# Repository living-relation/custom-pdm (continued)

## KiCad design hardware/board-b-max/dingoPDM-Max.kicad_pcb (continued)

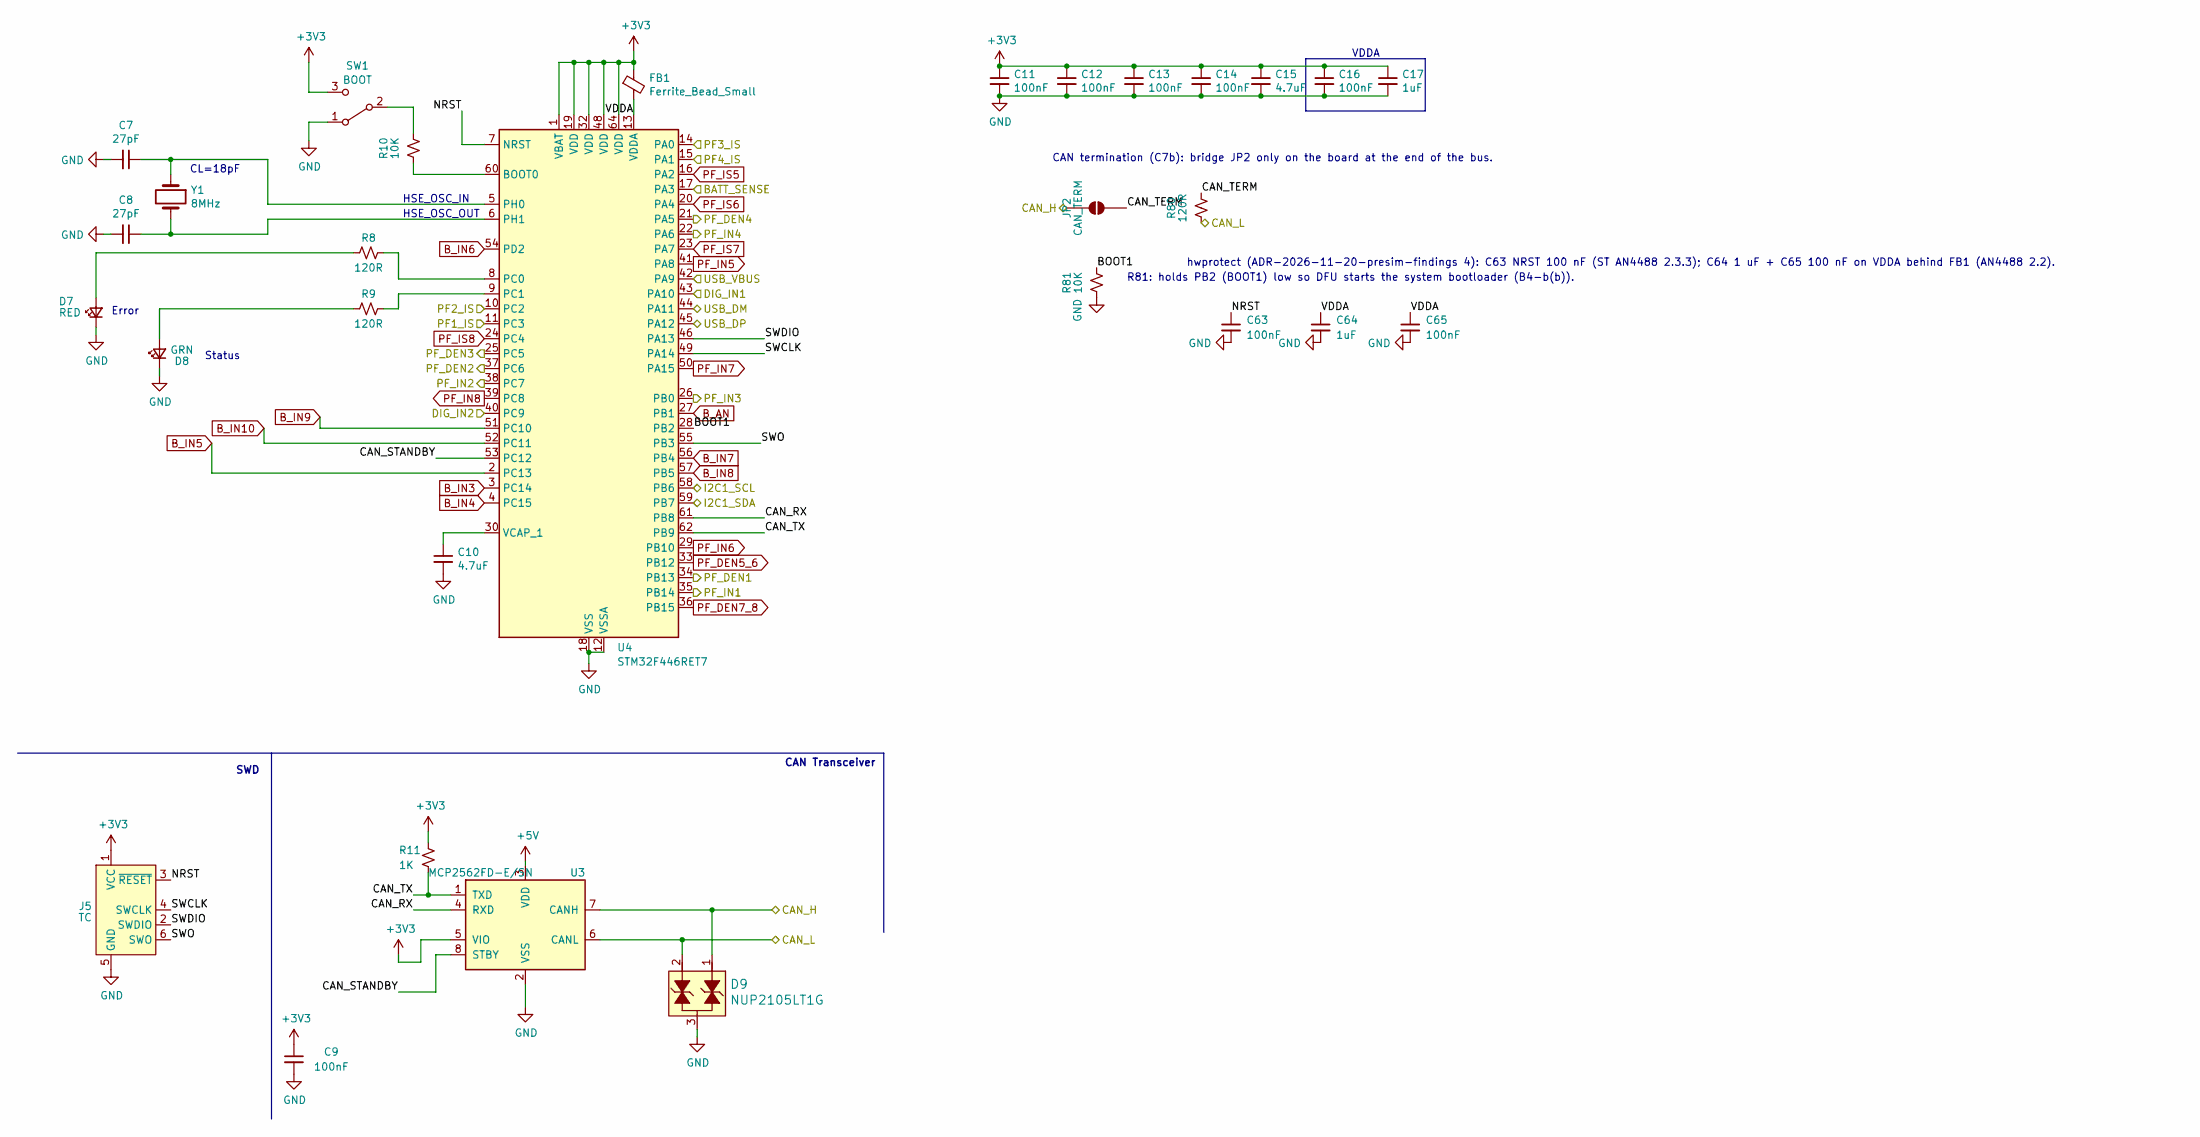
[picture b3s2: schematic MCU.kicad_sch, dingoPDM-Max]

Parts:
C7, C8: 27pF; C_0805_2012Metric; MPN 0805CG270J500NT; Digi-Key_PN 478-10518-1-ND
C9, C11, C12, C13, C14, C16: 100nF; C_0805_2012Metric; MPN CC0805KRX7R9BB104; Digi-Key_PN 478-1395-1-ND
C10, C15: 4.7uF; C_0805_2012Metric; MPN CL21B475KAFNNNE; LCSC C98195
C17: 1uF; C_0805_2012Metric; MPN CL21B105KBFNNNE; Digi-Key_PN 311-1365-1-ND
C63, C65: 100nF; C_0402_1005Metric; MPN CL05B104KO5NNNC; LCSC C1525
C64: 1uF; C_0402_1005Metric; MPN TCC0402X7R105K100AT; LCSC C47325373
D7: RED; LED_0805_2012Metric; MPN LS R976-NR-1-0-20-R18; Digi-Key_PN 475-1278-1-ND
D8: GRN; LED_0805_2012Metric; MPN LG R971-KN-1-0-20-R18; Digi-Key_PN 475-1410-1-ND
D9: NUP2105LT1G; SOT-23-3; MPN NUP2105LT1G; Digi-Key_PN NUP2105LT1GOSCT-ND
FB1: Ferrite_Bead_Small; R_0805_2012Metric; MPN BLM21PG221SN1D; Digi-Key_PN 490-1054-1-ND
J5: TC; Tag-Connect_TC2030-IDC-NL_2x03_P1.27mm_Vertical
JP2: CAN_TERM; SolderJumper-2_P1.3mm_Open_RoundedPad1.0x1.5mm
R8, R9, R80: 120R; R_0805_2012Metric; MPN 0805W8F1200T5E; Digi-Key_PN 311-120CRCT-ND
R10, R81: 10K; R_0805_2012Metric; MPN 0805W8F1002T5E; Digi-Key_PN 311-10.0KCRDKR-ND
R11: 1K; R_0805_2012Metric; MPN 0805W8F1001T5E; Digi-Key_PN 311-1.0KARCT-ND
SW1: BOOT; CJS-1200TB; MPN CJS-1200TB1; Digi-Key_PN 563-CJS-1200TB1CT-ND
U3: MCP2562FD-E/SN; SOIC-8_3.9x4.9mm_P1.27mm; MPN MCP2562FD-E/SN; Digi-Key_PN MCP2562FD-E/SN-ND
U4: STM32F446RET7; LQFP-64_10x10mm_P0.5mm; MPN STM32F446RET7; Digi-Key_PN 497-16775-ND
Y1: 8MHz; Crystal_SMD_5032-2Pin_5.0x3.2mm_HandSoldering; MPN ECS-80-18-30Q-CES-TR; Digi-Key_PN 50-ECS-80-18-30Q-CES-TRCT-ND

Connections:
+3V3: C9.1, C11.1, C12.1, C13.1, C14.1, C15.1, C16.1, C17.1, FB1.1, J5.1 (VCC), R11.2, SW1.3 (C), U3.5 (Vref), U4.1 (VBAT), U4.19 (VDD), U4.32 (VDD), U4.48 (VDD), U4.64 (VDD); also elsewhere on the board
+5V: U3.3 (VDD); also elsewhere on the board
/MCU/BATT_SENSE: U4.17 (PA3); also elsewhere on the board
/MCU/BOOT1: R81.1, U4.28 (PB2)
/MCU/CAN_RX: U3.4 (RXD), U4.61 (PB8)
/MCU/CAN_STANDBY: U3.8 (Rs), U4.53 (PC12)
/MCU/CAN_TERM: JP2.2 (B), R80.1
/MCU/CAN_TX: R11.1, U3.1 (TXD), U4.62 (PB9)
/MCU/NRST: C63.1, J5.3 (~RESET), U4.7 (NRST)
/MCU/SWCLK: J5.4 (SWCLK), U4.49 (PA14)
/MCU/SWDIO: J5.2 (SWDIO), U4.46 (PA13)
/MCU/SWO: J5.6 (SWO), U4.55 (PB3)
/MCU/VDDA: C64.1, C65.1, FB1.2, U4.13 (VDDA)
B_AN: U4.27 (PB1); also elsewhere on the board
B_IN3: U4.3 (PC14); also elsewhere on the board
B_IN4: U4.4 (PC15); also elsewhere on the board
B_IN5: U4.2 (PC13); also elsewhere on the board
B_IN6: U4.54 (PD2); also elsewhere on the board
B_IN7: U4.56 (PB4); also elsewhere on the board
B_IN8: U4.57 (PB5); also elsewhere on the board
B_IN9: U4.51 (PC10); also elsewhere on the board
B_IN10: U4.52 (PC11); also elsewhere on the board
CAN_H: D9.1, JP2.1 (A), U3.7 (CANH); also elsewhere on the board
CAN_L: D9.2, R80.2, U3.6 (CANL); also elsewhere on the board
GND: C7.2, C8.2, C9.2, C10.2, C11.2, C12.2, C13.2, C14.2, C15.2, C16.2, C17.2, C63.2, C64.2, C65.2, D7.1 (K), D8.1 (K), D9.3, J5.5 (GND), R81.2, SW1.1 (A), U3.2 (VSS), U4.12 (VSSA), U4.18 (VSS), U4.31 (VSS), U4.47 (VSS), U4.63 (VSS); also elsewhere on the board
I2C1_SCL: U4.58 (PB6); also elsewhere on the board
I2C1_SDA: U4.59 (PB7); also elsewhere on the board
IN_1: U4.43 (PA10); also elsewhere on the board
IN_2: U4.40 (PC9); also elsewhere on the board
unnamed: D7.2 (A), R8.2
unnamed: D8.2 (A), R9.2
unnamed: R10.1, SW1.2 (B)
unnamed: R10.2, U4.60 (BOOT0)
unnamed: R8.1, U4.8 (PC0)
unnamed: R9.1, U4.9 (PC1)
unnamed: C7.1, U4.5 (PH0), Y1.1
unnamed: C8.1, U4.6 (PH1), Y1.2
unnamed: C10.1, U4.30 (VCAP_1)
PF_DEN1: U4.34 (PB13); also elsewhere on the board
PF_DEN2: U4.37 (PC6); also elsewhere on the board
PF_DEN3: U4.25 (PC5); also elsewhere on the board
PF_DEN4: U4.21 (PA5); also elsewhere on the board
PF_DEN5_6: U4.33 (PB12); also elsewhere on the board
PF_DEN7_8: U4.36 (PB15); also elsewhere on the board
PF_IN1: U4.35 (PB14); also elsewhere on the board
PF_IN2: U4.38 (PC7); also elsewhere on the board
PF_IN3: U4.26 (PB0); also elsewhere on the board
PF_IN4: U4.22 (PA6); also elsewhere on the board
PF_IN5: U4.41 (PA8); also elsewhere on the board
PF_IN6: U4.29 (PB10); also elsewhere on the board
PF_IN7: U4.50 (PA15); also elsewhere on the board
PF_IN8: U4.39 (PC8); also elsewhere on the board
PF_IS1: U4.11 (PC3); also elsewhere on the board
PF_IS2: U4.10 (PC2); also elsewhere on the board
PF_IS3: U4.14 (PA0); also elsewhere on the board
PF_IS4: U4.15 (PA1); also elsewhere on the board
PF_IS5: U4.16 (PA2); also elsewhere on the board
PF_IS6: U4.20 (PA4); also elsewhere on the board
PF_IS7: U4.23 (PA7); also elsewhere on the board
PF_IS8: U4.24 (PC4); also elsewhere on the board
USB_D+: U4.45 (PA12); also elsewhere on the board
USB_D-: U4.44 (PA11); also elsewhere on the board
USB_VBUS: U4.42 (PA9); also elsewhere on the board

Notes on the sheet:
SWD
Error
CAN Transceiver
HSE_OSC_IN
CL=18pF
HSE_OSC_OUT
VDDA
Status
CAN termination (C7b): bridge JP2 only on the board at the end of the bus.
R81: holds PB2 (BOOT1) low so DFU starts the system bootloader (B4-b(b)).
hwprotect (ADR-2026-11-20-presim-findings 4): C63 NRST 100 nF (ST AN4488 2.3.3); C64 1 uF + C65 100 nF on VDDA behind FB1 (AN4488 2.2).

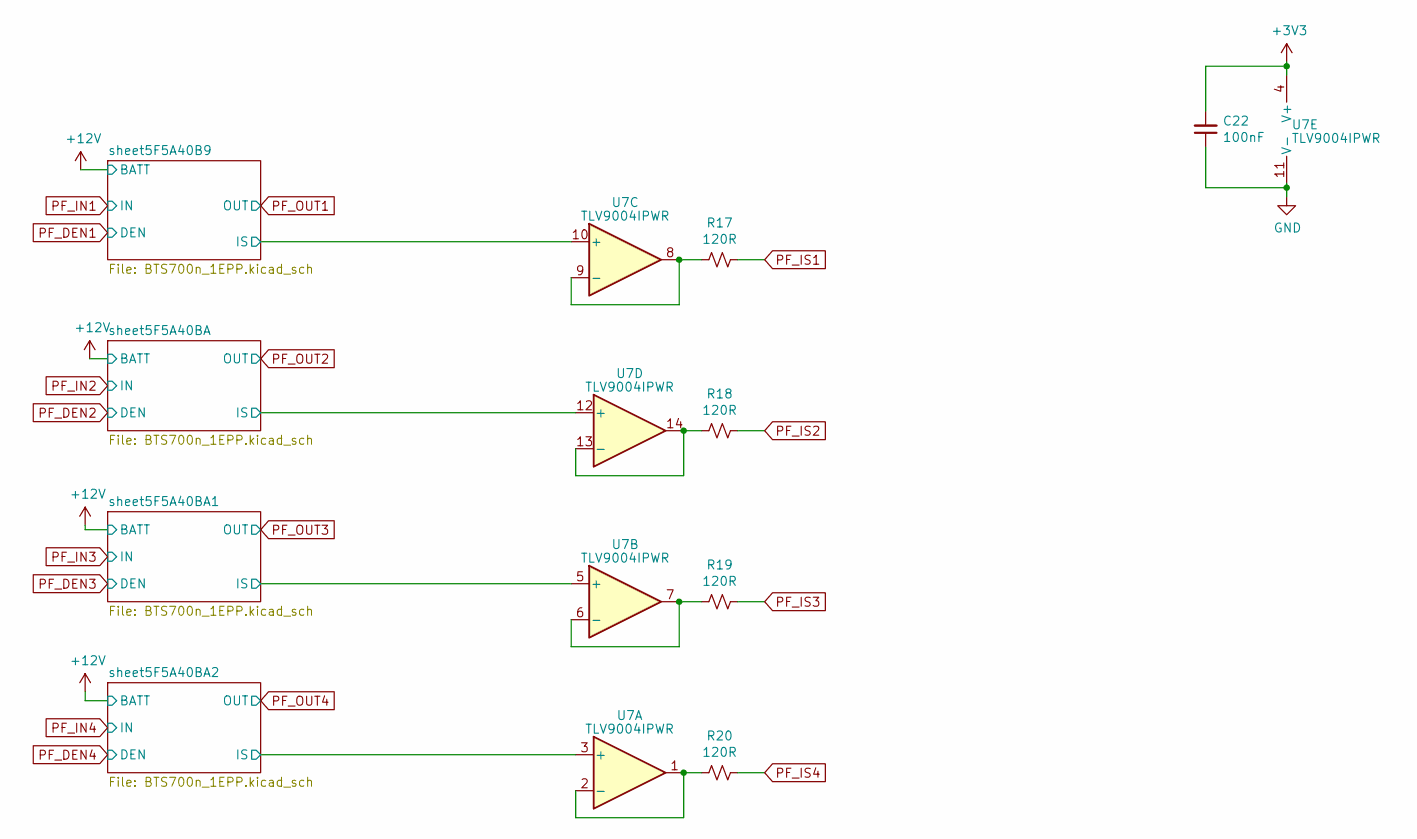
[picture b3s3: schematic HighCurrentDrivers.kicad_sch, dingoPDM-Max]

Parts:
C22: 100nF; C_0805_2012Metric; MPN CC0805KRX7R9BB104; Digi-Key_PN 478-1395-1-ND
R17, R18, R19, R20: 120R; R_0805_2012Metric; MPN 0805W8F1200T5E; Digi-Key_PN 311-120CRCT-ND
U7: TLV9004IPWR; TSSOP-14_4.4x5mm_P0.65mm; MPN TLV9004IPWR; Digi-Key_PN 296-51827-1-ND

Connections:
+3V3: C22.2, U7.4 (V+); also elsewhere on the board
/HighCurrentDrivers/sheet5F5A40B9/IS: U7.10 (+); also elsewhere on the board
/HighCurrentDrivers/sheet5F5A40BA1/IS: U7.5 (+); also elsewhere on the board
/HighCurrentDrivers/sheet5F5A40BA2/IS: U7.3 (+); also elsewhere on the board
/HighCurrentDrivers/sheet5F5A40BA/IS: U7.12 (+); also elsewhere on the board
GND: C22.1, U7.11 (V-); also elsewhere on the board
unnamed: R20.2, U7.1, U7.2 (-)
unnamed: R19.2, U7.6 (-), U7.7
unnamed: R17.2, U7.8, U7.9 (-)
unnamed: R18.2, U7.13 (-), U7.14
PF_IS1: R17.1; also elsewhere on the board
PF_IS2: R18.1; also elsewhere on the board
PF_IS3: R19.1; also elsewhere on the board
PF_IS4: R20.1; also elsewhere on the board

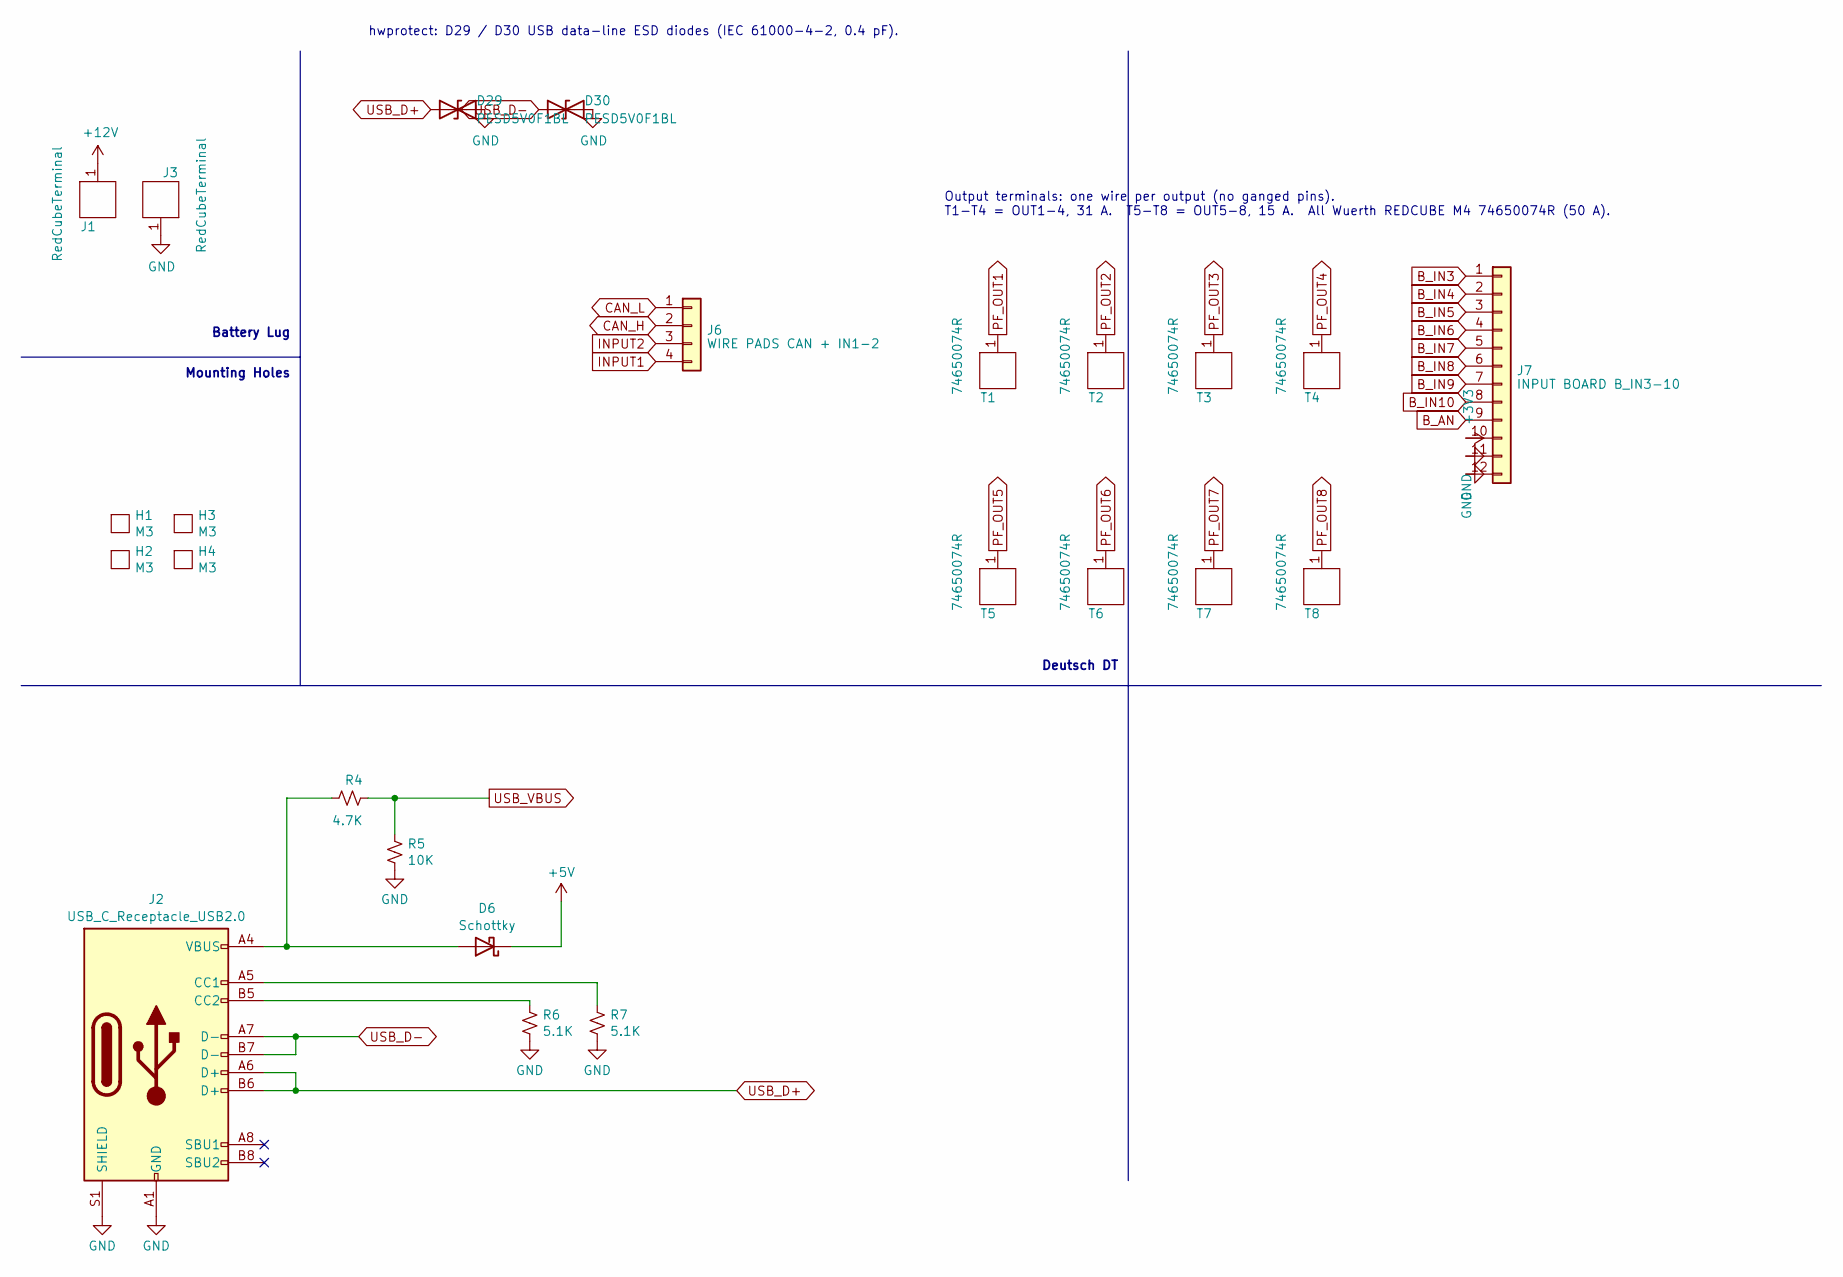
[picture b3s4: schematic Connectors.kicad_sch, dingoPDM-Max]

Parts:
D6: Schottky; D_SOD-123; MPN PMEG10010ELRX; Digi-Key_PN 1727-2394-1-ND
D29, D30: PESD5V0F1BL; D_SOD-882; MPN PESD5V0F1BL,315; LCSC C45961
H1, H2, H3, H4: M3; MountingHole_3.2mm_M3_ISO7380_Pad
J1, J3: RedCubeTerminal; M6_Hole_8Pin_7461084; MPN 7461084; Digi-Key_PN 732-3203-ND
J2: USB_C_Receptacle_USB2.0; USB_C_Receptacle_GCT_USB4085; MPN USB4085-GF-A; Digi-Key_PN 2073-USB4085-GF-ACT-ND
J6: WIRE PADS CAN + IN1-2; MicroFit_2x02_WirePads
J7: INPUT BOARD B_IN3-10; JST_GH_BM12B-GHS-TBT_1x12-1MP_P1.25mm_Vertical; MPN BM12B-GHS-TBT; LCSC C20089173
R4: 4.7K; R_0805_2012Metric; MPN 0805W8F4701T5E; Digi-Key_PN 311-4.70KCRCT-ND
R5: 10K; R_0805_2012Metric; MPN 0805W8F1002T5E; Digi-Key_PN 311-10.0KCRDKR-ND
R6, R7: 5.1K; R_0805_2012Metric; MPN ARG05FTC5101; Digi-Key_PN 311-5.1KARCT-ND
T1, T2, T3, T4, T5, T6, T7, T8: 74650074R; Wuerth_REDCUBE-THR_WP-THRBU_74650074_THR; MPN 74650074R; Digi-Key_PN 732-74650074RCT-ND

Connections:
+3V3: J7.10; also elsewhere on the board
+5V: D6.1 (K); also elsewhere on the board
+12V: J1.1; also elsewhere on the board
B_AN: J7.9; also elsewhere on the board
B_IN3: J7.1; also elsewhere on the board
B_IN4: J7.2; also elsewhere on the board
B_IN5: J7.3; also elsewhere on the board
B_IN6: J7.4; also elsewhere on the board
B_IN7: J7.5; also elsewhere on the board
B_IN8: J7.6; also elsewhere on the board
B_IN9: J7.7; also elsewhere on the board
B_IN10: J7.8; also elsewhere on the board
CAN_H: J6.2; also elsewhere on the board
CAN_L: J6.1; also elsewhere on the board
GND: D29.2 (A2), D30.2 (A2), J2.A1 (GND), J2.A12 (GND), J2.B1 (GND), J2.B12 (GND), J2.S1 (SHIELD), J3.1, J7.11, J7.12, R5.2, R6.2, R7.2; also elsewhere on the board
INPUT1: J6.4; also elsewhere on the board
INPUT2: J6.3; also elsewhere on the board
unnamed: D6.2 (A), J2.A4 (VBUS), J2.A9 (VBUS), J2.B4 (VBUS), J2.B9 (VBUS), R4.1
unnamed: J2.A5 (CC1), R7.1
unnamed: J2.B5 (CC2), R6.1
PF_OUT1: T1.1; also elsewhere on the board
PF_OUT2: T2.1; also elsewhere on the board
PF_OUT3: T3.1; also elsewhere on the board
PF_OUT4: T4.1; also elsewhere on the board
PF_OUT5: T5.1; also elsewhere on the board
PF_OUT6: T6.1; also elsewhere on the board
PF_OUT7: T7.1; also elsewhere on the board
PF_OUT8: T8.1; also elsewhere on the board
USB_D+: D29.1 (A1), J2.A6 (D+), J2.B6 (D+); also elsewhere on the board
USB_D-: D30.1 (A1), J2.A7 (D-), J2.B7 (D-); also elsewhere on the board
USB_VBUS: R4.2, R5.1; also elsewhere on the board

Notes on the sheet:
Deutsch DT
Battery Lug
Mounting Holes
Output terminals: one wire per output (no ganged pins). T1-T4 = OUT1-4, 31 A. T5-T8 = OUT5-8, 15 A. All Wuerth REDCUBE M4 74650074R (50 A).
hwprotect: D29 / D30 USB data-line ESD diodes (IEC 61000-4-2, 0.4 pF).

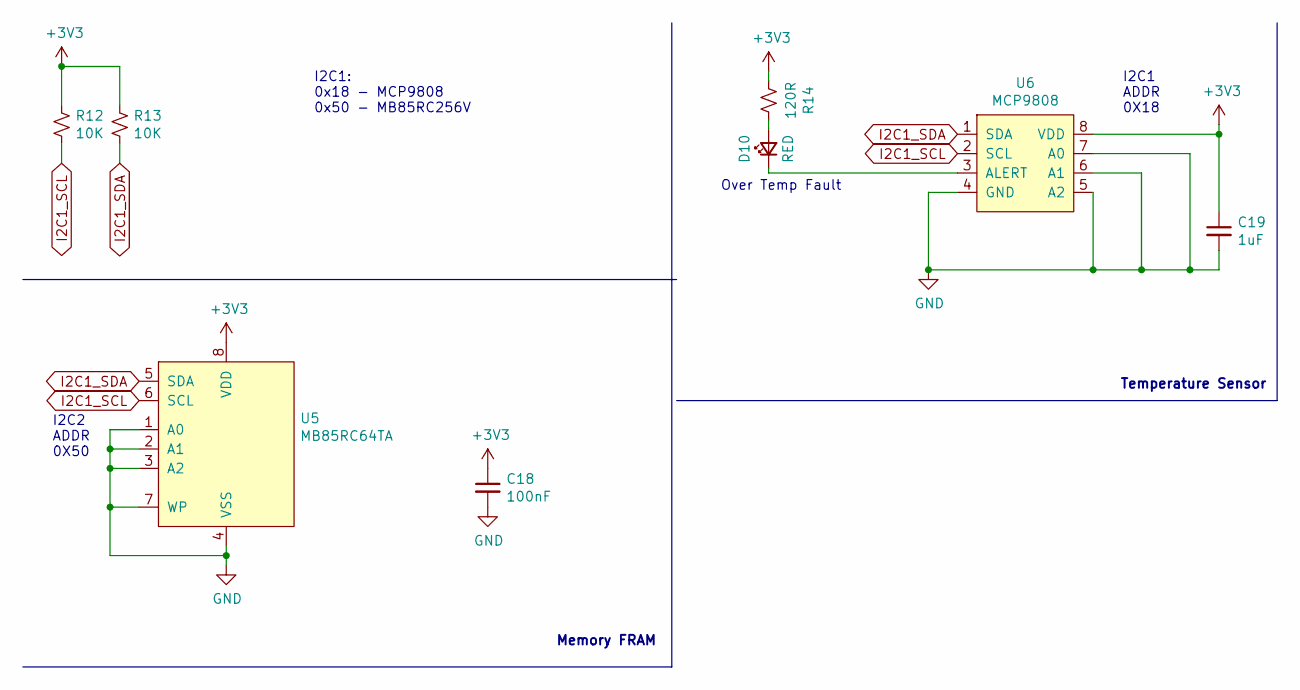
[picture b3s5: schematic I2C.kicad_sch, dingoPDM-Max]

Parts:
C18: 100nF; C_0805_2012Metric; MPN CC0805KRX7R9BB104; Digi-Key_PN 478-1395-1-ND
C19: 1uF; C_0805_2012Metric; MPN CL21B105KBFNNNE; Digi-Key_PN 311-1365-1-ND
D10: RED; LED_0805_2012Metric; MPN LS R976-NR-1-0-20-R18; Digi-Key_PN 475-1278-1-ND
R12, R13: 10K; R_0805_2012Metric; MPN 0805W8F1002T5E; Digi-Key_PN 311-10.0KCRDKR-ND
R14: 120R; R_0805_2012Metric; MPN 0805W8F1200T5E; Digi-Key_PN 311-120CRCT-ND
U5: MB85RC64TA; SOIC-8_3.9x4.9mm_P1.27mm; MPN MB85RC64TAPNF-G-AWERE2; Digi-Key_PN 865-MB85RC64TAPNF-G-AWERE2TR-ND
U6: MCP9808; MSOP-8_3x3mm_P0.65mm; MPN MCP9808T-E/MS; Digi-Key_PN MCP9808T-E/MSCT-ND

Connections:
+3V3: C18.1, C19.1, R12.1, R13.1, R14.2, U5.8 (VDD), U6.8 (VDD); also elsewhere on the board
GND: C18.2, C19.2, U5.1 (A0), U5.2 (A1), U5.3 (A2), U5.4 (VSS), U5.7 (WP), U6.4 (GND), U6.5 (A2), U6.6 (A1), U6.7 (A0); also elsewhere on the board
I2C1_SCL: R12.2, U5.6 (SCL), U6.2 (SCL); also elsewhere on the board
I2C1_SDA: R13.2, U5.5 (SDA), U6.1 (SDA); also elsewhere on the board
unnamed: D10.2 (A), R14.1
unnamed: D10.1 (K), U6.3 (ALERT)

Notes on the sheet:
I2C1 ADDR 0X18
I2C2 ADDR 0X50
Over Temp Fault
Temperature Sensor
I2C1: 0x18 - MCP9808 0x50 - MB85RC256V
Memory FRAM

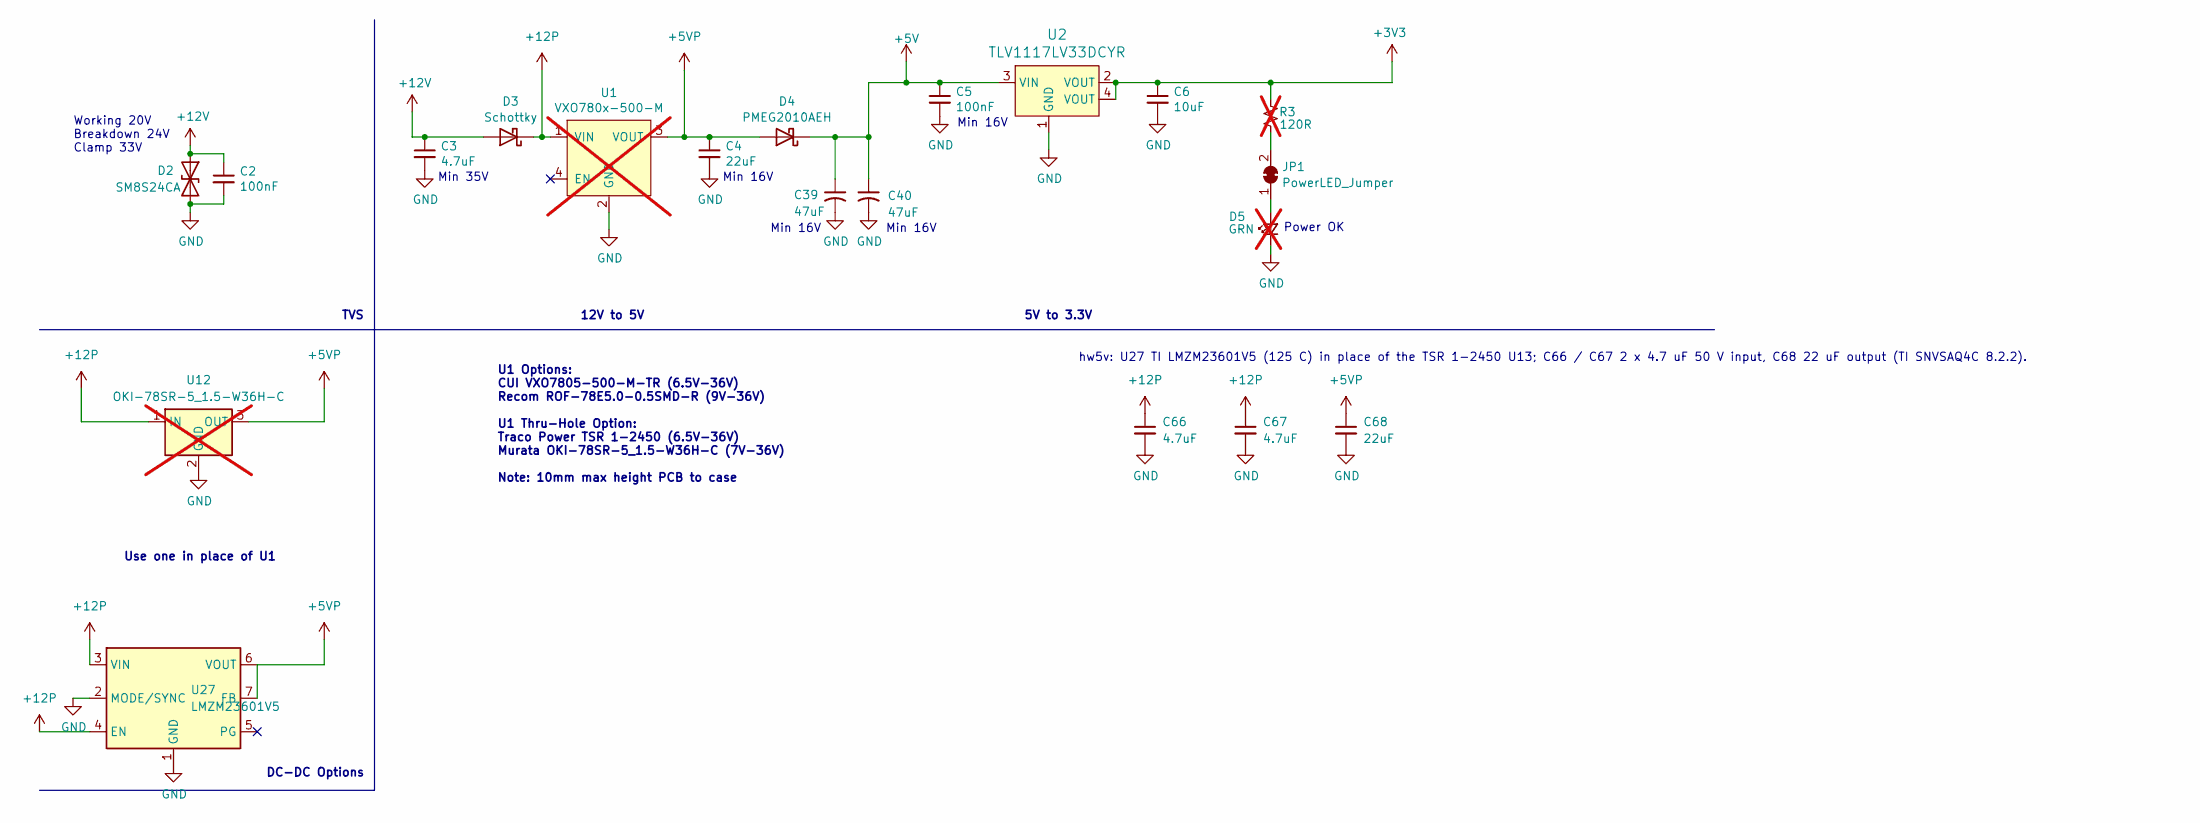
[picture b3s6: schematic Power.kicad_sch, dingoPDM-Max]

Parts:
C2, C5: 100nF; C_0805_2012Metric; MPN CC0805KRX7R9BB104; Digi-Key_PN 478-1395-1-ND
C3, C66, C67: 4.7uF; C_0805_2012Metric; MPN CGA4J1X7R1H475KT0Y0N; LCSC C694229
C4, C68: 22uF; C_0805_2012Metric; MPN GRM21BZ71A226ME15L; LCSC C907991
C6: 10uF; C_0805_2012Metric; MPN CL21B106KPQNNNE; LCSC C32635
C39, C40: 47uF; C_2220_5750Metric; MPN FS55X476K250LRG; Digi-Key_PN 445-7935-1-ND
D2: SM8S24CA; D_DO-218AB_Vishay_SM8S; MPN SM8S24CA-Q; Digi-Key_PN SM8S24CA-QCT-ND
D3: Schottky; D_SOD-123; MPN PMEG10010ELRX; Digi-Key_PN 1727-2394-1-ND
D4: PMEG2010AEH; D_SOD-123F; MPN PMEG2010AEH,115; Digi-Key_PN 1727-PMEG2010AEH,115CT-ND
D5: GRN; LED_0805_2012Metric; MPN LG R971-KN-1-0-20-R18; Digi-Key_PN 475-1410-1-ND; not fitted
JP1: PowerLED_Jumper; SolderJumper-2_P1.3mm_Bridged_RoundedPad1.0x1.5mm
R3: 120R; R_0805_2012Metric; MPN 0805W8F1200T5E; Digi-Key_PN 311-120CRCT-ND; not fitted
U1: VXO780x-500-M; VXO78x-500-M; MPN VXO7805-500-M-TR; Digi-Key_PN 102-VXO7805-500-M-CT-ND; not fitted
U2: TLV1117LV33DCYR; SOT-223; MPN TLV1117LV33DCYR; Digi-Key_PN 296-28778-1-ND
U12: OKI-78SR-5_1.5-W36H-C; Converter_DCDC_Murata_OKI-78SR_Horizontal; MPN OKI-78SR-5/1.5-W36H-C; Digi-Key_PN 811-2692-ND; not fitted
U27: LMZM23601V5; Texas_SIL0010A_MicroSiP-10-1EP_3.8x3mm_P0.6mm_EP0.7x2.9mm_TI; MPN LMZM23601V5SILR; LCSC C2868357

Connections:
+3V3: C6.1, R3.2, U2.2 (VOUT), U2.4 (VOUT); also elsewhere on the board
+5V: C5.1, C39.1, C40.1, D4.1 (K), U2.3 (VIN); also elsewhere on the board
+5VP: C4.1, C68.1, D4.2 (A), U1.3 (VOUT), U12.3 (OUT), U27.6 (VOUT), U27.7 (FB)
+12P: C66.1, C67.1, D3.1 (K), U1.1 (VIN), U12.1 (IN), U27.3 (VIN), U27.4 (EN)
+12V: C2.1, C3.1, D2.1 (A1), D3.2 (A); also elsewhere on the board
GND: C2.2, C3.2, C4.2, C5.2, C6.2, C39.2, C40.2, C66.2, C67.2, C68.2, D2.2 (A2), D5.1 (K), U1.2 (GND), U2.1 (GND), U12.2 (GND), U27.1 (GND), U27.2 (MODE/SYNC), U27.11 (GND); also elsewhere on the board
unnamed: D5.2 (A), JP1.1 (A)
unnamed: JP1.2 (B), R3.1

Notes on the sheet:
Min 16V
TVS
Min 35V
Power OK
Use one in place of U1
5V to 3.3V
12V to 5V
Working 20V Breakdown 24V Clamp 33V
DC-DC Options
U1 Options: CUI VXO7805-500-M-TR (6.5V-36V) Recom ROF-78E5.0-0.5SMD-R (9V-36V) U1 Thru-Hole Option: Traco Power TSR 1-2450 (6.5V-36V) Murata OKI-78SR-5_1.5-W36H-C (7V-36V) Note: 10mm max height PCB to case
hw5v: U27 TI LMZM23601V5 (125 C) in place of the TSR 1-2450 U13; C66 / C67 2 x 4.7 uF 50 V input, C68 22 uF output (TI SNVSAQ4C 8.2.2).

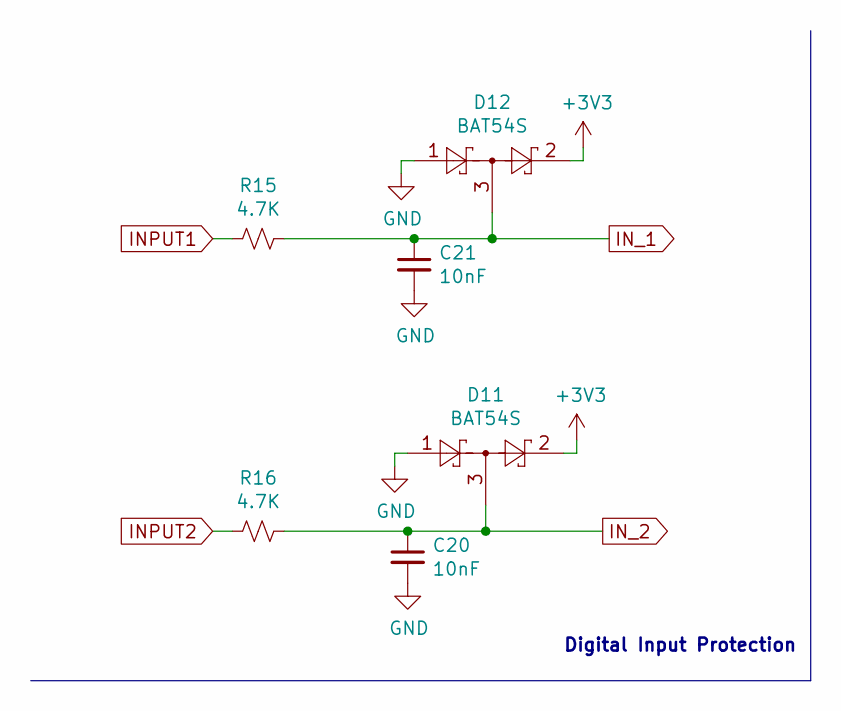
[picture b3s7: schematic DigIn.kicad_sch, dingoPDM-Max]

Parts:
C20, C21: 10nF; C_0805_2012Metric; MPN CL21B103KBANNNC; Digi-Key_PN 311-1136-1-ND
D11, D12: BAT54S; SOT-23; MPN BAT54S,215; Digi-Key_PN BAT54SLT1GOSCT-ND
R15, R16: 4.7K; R_0805_2012Metric; MPN 0805W8F4701T5E; Digi-Key_PN 311-4.70KCRCT-ND

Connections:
+3V3: D11.2, D12.2; also elsewhere on the board
GND: C20.2, C21.2, D11.1, D12.1; also elsewhere on the board
INPUT1: R15.2; also elsewhere on the board
INPUT2: R16.2; also elsewhere on the board
IN_1: C21.1, D12.3, R15.1; also elsewhere on the board
IN_2: C20.1, D11.3, R16.1; also elsewhere on the board

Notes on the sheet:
Digital Input Protection

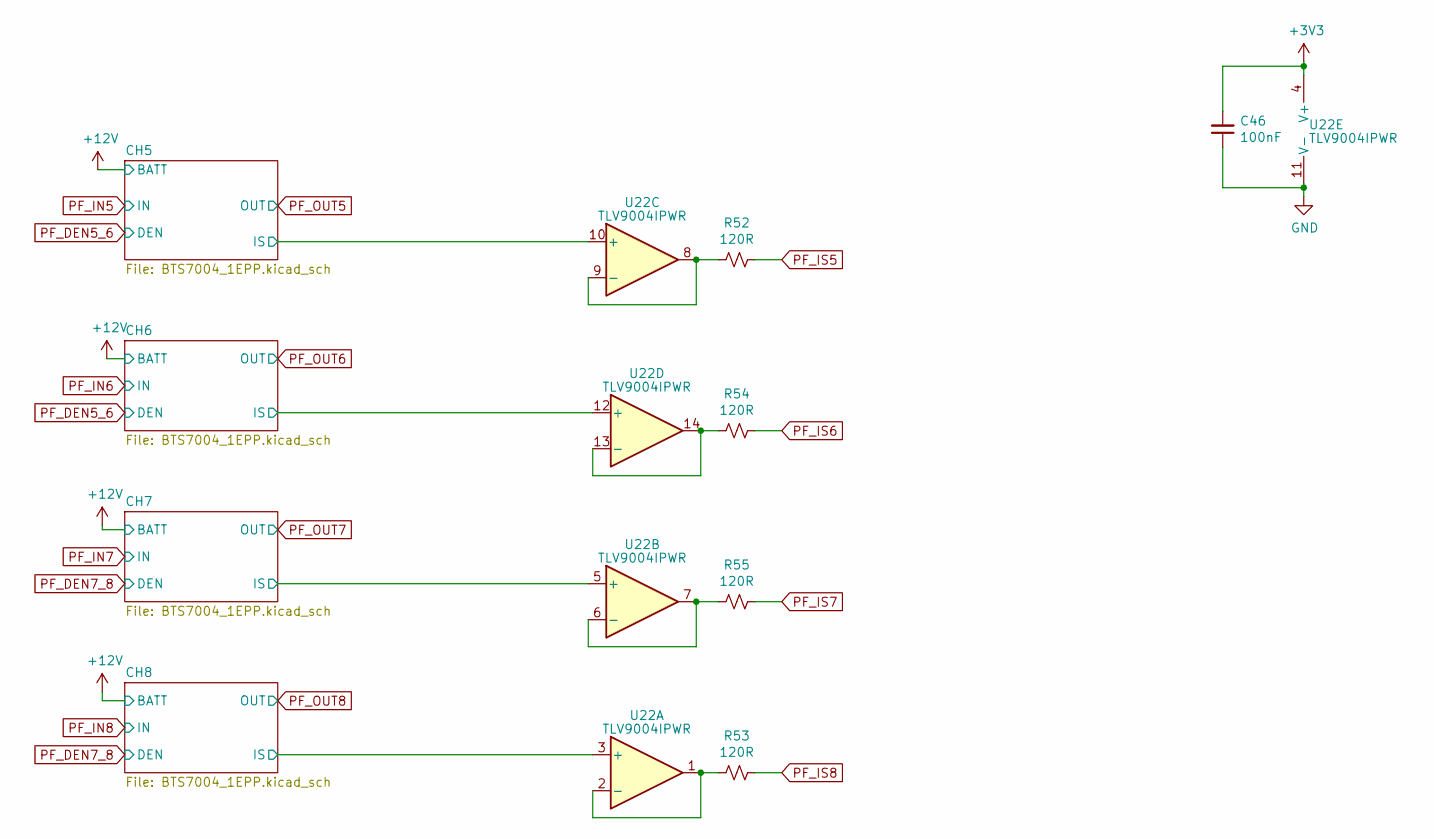
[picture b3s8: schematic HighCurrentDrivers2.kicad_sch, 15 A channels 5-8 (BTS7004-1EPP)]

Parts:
C46: 100nF; C_0805_2012Metric; MPN CC0805KRX7R9BB104; Digi-Key_PN 478-1395-1-ND
R52, R53, R54, R55: 120R; R_0805_2012Metric; MPN 0805W8F1200T5E; Digi-Key_PN 311-120CRCT-ND
U22: TLV9004IPWR; TSSOP-14_4.4x5mm_P0.65mm; MPN TLV9004IPWR; Digi-Key_PN 296-51827-1-ND

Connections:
+3V3: C46.2, U22.4 (V+); also elsewhere on the board
/HighCurrentDrivers2/CH5/IS: U22.10 (+); also elsewhere on the board
/HighCurrentDrivers2/CH6/IS: U22.12 (+); also elsewhere on the board
/HighCurrentDrivers2/CH7/IS: U22.5 (+); also elsewhere on the board
/HighCurrentDrivers2/CH8/IS: U22.3 (+); also elsewhere on the board
GND: C46.1, U22.11 (V-); also elsewhere on the board
unnamed: R53.2, U22.1, U22.2 (-)
unnamed: R55.2, U22.6 (-), U22.7
unnamed: R52.2, U22.8, U22.9 (-)
unnamed: R54.2, U22.13 (-), U22.14
PF_IS5: R52.1; also elsewhere on the board
PF_IS6: R54.1; also elsewhere on the board
PF_IS7: R55.1; also elsewhere on the board
PF_IS8: R53.1; also elsewhere on the board

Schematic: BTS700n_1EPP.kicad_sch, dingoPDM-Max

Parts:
C23: 47nF; C_0805_2012Metric; MPN C0805C473K5RAC7800; Digi-Key_PN 399-C0805C473K5RACTUCT-ND
C24: 100nF; C_0805_2012Metric; MPN CC0805KRX7R9BB104; Digi-Key_PN 478-1395-1-ND
C25: 10nF; C_0805_2012Metric; MPN CL21B103KBANNNC; Digi-Key_PN 311-1136-1-ND
C26: 220pF; C_0805_2012Metric; MPN CC0805GRNPO0BN221; Digi-Key_PN 399-1138-1-ND
D13: BYG23M; DO-214AC; MPN BYG23M-E3/TR; Digi-Key_PN BYG23M-E3/TR3GICT-ND
D14: 5.1V; D_SOD-323_HandSoldering; MPN PDZ5.1B,115; Digi-Key_PN 1727-5155-1-ND
R21, R22, R25, R26: 4.7K; R_0805_2012Metric; MPN 0805W8F4701T5E; Digi-Key_PN 311-4.70KCRCT-ND
R23: 1.2K; R_0805_2012Metric; MPN 0805W8F1201T5E; Digi-Key_PN 311-1.20KCRCT-ND
R24: 47R 1/4W; R_1206_3216Metric; MPN FRC1206J470 TS; Digi-Key_PN 311-47.0FRCT-ND
U8: BTS70012-1ESP; TSDSO-24; MPN BTS700121ESPXUMA1; Digi-Key_PN 448-BTS700121ESPXUMA2CT-ND

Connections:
+12V: C23.2, C24.2, U8.25 (VS); also elsewhere on the board
/HighCurrentDrivers/sheet5F5A40B9/IS: C26.2, R26.1; also elsewhere on the board
GND: C24.1, C25.1, C26.1, D13.A, D14.2 (A), R23.2, R24.1; also elsewhere on the board
unnamed: D14.1 (K), R25.1, R26.2
unnamed: R22.1, U8.6 (DEN)
unnamed: C23.1, R24.2, U8.4 (GND)
unnamed: R21.1, U8.5 (IN)
unnamed: R23.1, R25.2, U8.7 (IS)
PF_DEN1: R22.2; also elsewhere on the board
PF_IN1: R21.2; also elsewhere on the board
PF_OUT1: C25.2, D13.K, U8.13 (OUT1), U8.14 (OUT2), U8.15 (OUT3), U8.16 (OUT4), U8.17 (OUT5), U8.18 (OUT6), U8.19 (OUT7), U8.20 (OUT8), U8.21 (OUT9), U8.22 (OUT10), U8.23 (OUT11), U8.24 (OUT12); also elsewhere on the board

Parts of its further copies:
C27, C31, C35: 47nF; C_0805_2012Metric; MPN C0805C473K5RAC7800; Digi-Key_PN 399-C0805C473K5RACTUCT-ND
C28, C32, C36: 100nF; C_0805_2012Metric; MPN CC0805KRX7R9BB104; Digi-Key_PN 478-1395-1-ND
C29, C33, C37: 10nF; C_0805_2012Metric; MPN CL21B103KBANNNC; Digi-Key_PN 311-1136-1-ND
C30, C34, C38: 220pF; C_0805_2012Metric; MPN CC0805GRNPO0BN221; Digi-Key_PN 399-1138-1-ND
D15, D17, D19: BYG23M; DO-214AC; MPN BYG23M-E3/TR; Digi-Key_PN BYG23M-E3/TR3GICT-ND
D16, D18, D20: 5.1V; D_SOD-323_HandSoldering; MPN PDZ5.1B,115; Digi-Key_PN 1727-5155-1-ND
R27, R28, R31, R32, R33, R34, R37, R38, R39, R40, R43, R44: 4.7K; R_0805_2012Metric; MPN 0805W8F4701T5E; Digi-Key_PN 311-4.70KCRCT-ND
R29, R35, R41: 1.2K; R_0805_2012Metric; MPN 0805W8F1201T5E; Digi-Key_PN 311-1.20KCRCT-ND
R30, R36, R42: 47R 1/4W; R_1206_3216Metric; MPN FRC1206J470 TS; Digi-Key_PN 311-47.0FRCT-ND
U9, U10, U11: BTS70012-1ESP; TSDSO-24; MPN BTS700121ESPXUMA1; Digi-Key_PN 448-BTS700121ESPXUMA2CT-ND

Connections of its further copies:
+12V: C27.2, C28.2, C31.2, C32.2, C35.2, C36.2, U9.25 (VS), U10.25 (VS), U11.25 (VS); also elsewhere on the board
/HighCurrentDrivers/sheet5F5A40BA1/IS: C34.2, R38.1; also elsewhere on the board
/HighCurrentDrivers/sheet5F5A40BA2/IS: C38.2, R44.1; also elsewhere on the board
/HighCurrentDrivers/sheet5F5A40BA/IS: C30.2, R32.1; also elsewhere on the board
GND: C28.1, C29.1, C30.1, C32.1, C33.1, C34.1, C36.1, C37.1, C38.1, D15.A, D16.2 (A), D17.A, D18.2 (A), D19.A, D20.2 (A), R29.2, R30.1, R35.2, R36.1, R41.2, R42.1; also elsewhere on the board
unnamed: D16.1 (K), R31.1, R32.2
unnamed: D18.1 (K), R37.1, R38.2
unnamed: D20.1 (K), R43.1, R44.2
unnamed: R28.1, U9.6 (DEN)
unnamed: C27.1, R30.2, U9.4 (GND)
unnamed: R27.1, U9.5 (IN)
unnamed: R29.1, R31.2, U9.7 (IS)
unnamed: R34.1, U10.6 (DEN)
unnamed: C31.1, R36.2, U10.4 (GND)
unnamed: R33.1, U10.5 (IN)
unnamed: R35.1, R37.2, U10.7 (IS)
unnamed: R40.1, U11.6 (DEN)
unnamed: C35.1, R42.2, U11.4 (GND)
unnamed: R39.1, U11.5 (IN)
unnamed: R41.1, R43.2, U11.7 (IS)
PF_DEN2: R28.2; also elsewhere on the board
PF_DEN3: R34.2; also elsewhere on the board
PF_DEN4: R40.2; also elsewhere on the board
PF_IN2: R27.2; also elsewhere on the board
PF_IN3: R33.2; also elsewhere on the board
PF_IN4: R39.2; also elsewhere on the board
PF_OUT2: C29.2, D15.K, U9.13 (OUT1), U9.14 (OUT2), U9.15 (OUT3), U9.16 (OUT4), U9.17 (OUT5), U9.18 (OUT6), U9.19 (OUT7), U9.20 (OUT8), U9.21 (OUT9), U9.22 (OUT10), U9.23 (OUT11), U9.24 (OUT12); also elsewhere on the board
PF_OUT3: C33.2, D17.K, U10.13 (OUT1), U10.14 (OUT2), U10.15 (OUT3), U10.16 (OUT4), U10.17 (OUT5), U10.18 (OUT6), U10.19 (OUT7), U10.20 (OUT8), U10.21 (OUT9), U10.22 (OUT10), U10.23 (OUT11), U10.24 (OUT12); also elsewhere on the board
PF_OUT4: C37.2, D19.K, U11.13 (OUT1), U11.14 (OUT2), U11.15 (OUT3), U11.16 (OUT4), U11.17 (OUT5), U11.18 (OUT6), U11.19 (OUT7), U11.20 (OUT8), U11.21 (OUT9), U11.22 (OUT10), U11.23 (OUT11), U11.24 (OUT12); also elsewhere on the board

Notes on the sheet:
RC Filter
Flyback
